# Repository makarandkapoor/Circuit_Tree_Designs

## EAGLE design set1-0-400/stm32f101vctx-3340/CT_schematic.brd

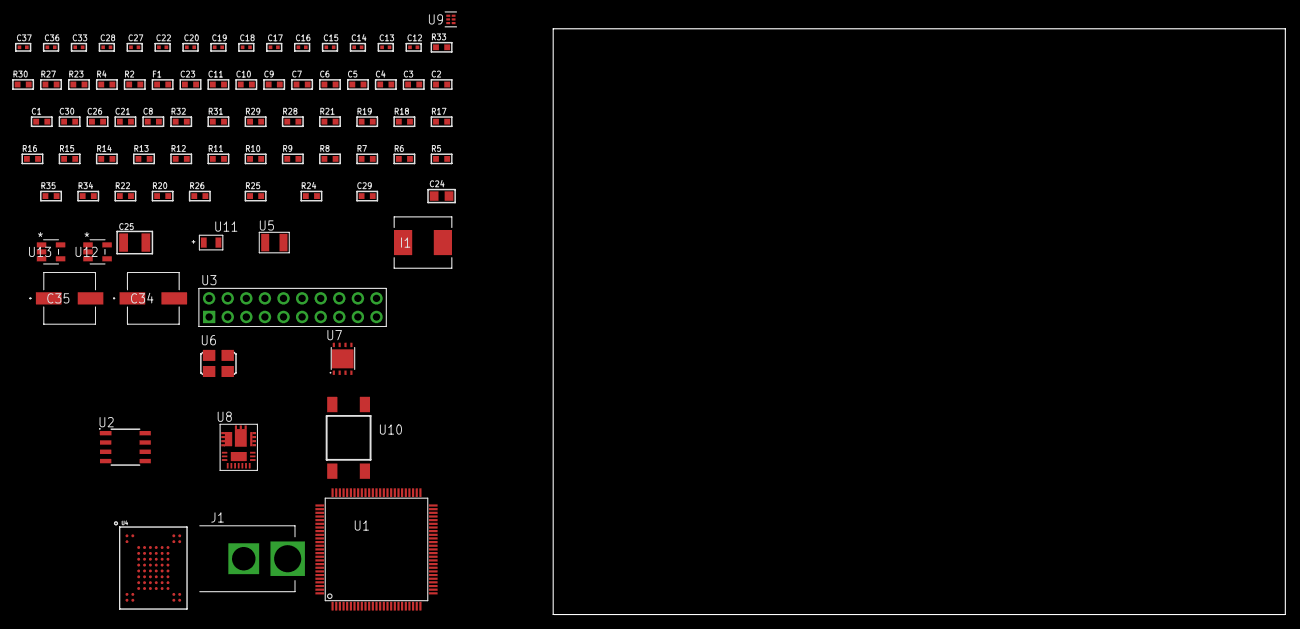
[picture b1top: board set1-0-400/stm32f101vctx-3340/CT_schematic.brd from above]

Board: 2 copper layers, 100.0 x 80.0 mm, 84 parts (0 on the bottom side), 45 nets, no tracks yet.

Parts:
C1, C11: 1e-06; C0603
C2, C3, C4, C5, C6, C7: 1e-07; C0603
C8: 4.7e-06; C0603
C9, C10: 1e-08; C0603
C12, C13: 1e-11; C0402
C14, C22, C36, C37: 1e-08; C0402
C15, C16, C17, C18, C19, C20, C27, C28, C33: 1e-07; C0402
C21, C26: 2.2e-06; C0603
C23: 8e-07; R0603
C24: 1e-05; C0805
C25: 0.0001; C1210
C29: 7.8444498006919e-09; R0603
C30: 2.7e-07; C0603
C34, C35: 0.0001; EXV-9H
F1: 240.0; L0603
I1: 6.8e-07; IND25X25CZ
J1: PJ-037B; PJ-037B_PACKAGE
R2: 1000.0; R0603
R4: 4700.0; R0603
R5, R6, R7, R8, R9, R10, R11, R12, R13, R14, R15, R16, R17, R18, R19, R31, R32: 10000.0; R0603
R20, R22: 100000.0; R0603
R21: 36000.0; R0603
R23: 0.1; R0603
R24: 4030.2416170974; R0603
R25: 719.68600305311; R0603
R26: 64.984347826087; R0603
R27: 130.0; R0603
R28: 39000.0; R0603
R29: 49900.0; R0603
R30: 5600.0; R0603
R33: 9100.0; R0603
R34: 680000.0; R0603
R35: 120000.0; R0603
U1: STM32F101VCT6; LQFP100
U2: AT25M02-SSHD-T; SOIC-8
U3: TST-110-05-T-D-RA
U4: mt29f4g08abbdah4; VFBGA-63
U5: ABS07-32.768KHZ-7-T
U6: ASFL1-25MHZ-NCS; ASFL1
U7: LP2951ACSDX/NOPB; WSON-8
U8: IR3899MTR1PBF
U9: TPS3895ADRYR; SON-6
U10: 4-1437565-2; SW_4-1437565-2
U11: Q65110A2395; LGM67K-G1J2-24-Z
U12, U13: nc7sz125m5x; NC7SZ125M5X

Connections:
CLK_CRYSTAL_U1_8: C12.1, U1.8, U5.1
CLK_CRYSTAL_U1_9: C13.1, U1.9, U5.2
CLK_U1_12: U1.12, U6.3
GND: C1.2, C2.2, C3.2, C4.2, C5.2, C6.2, C7.2, C8.2, C9.2, C10.2, C11.2, C12.2, C13.2, C14.2, C15.2, C16.2, C17.2, C18.2, C19.2, C20.2, C21.2, C22.2, C23.2, C24.2, C26.2, C27.2, C28.2, C33.2, C34.2, C35.2, C36.2, C37.2, J1.2, R2.2, R5.2, R14.2, R22.2, R23.1, R23.2, R25.2, R28.2, R30.2, R33.2, R35.2, U1.10, U1.19, U1.20, U1.27, U1.49, U1.74, U1.99, U2.4, U3.4, U3.6, U3.8, U3.10, U3.12, U3.14, U3.16, U3.18, U3.20, U4.C5, U4.F7, U4.K3, U4.K8, U6.2, U7.3, U7.4, U7.PAD, U8.4, U8.11, U8.17, U9.2, U11.C, U12.2, U12.3, U13.1, U13.3
NET_U1_14: R4.1, U1.14, U13.4
NET_U1_22: C9.1, C10.1, C11.1, F1.1, U1.21, U1.22
NET_U1_94: R5.1, U1.94
NET_U1_98: U10.3, U10.4
NET_U2_3: R6.1, U2.3
NET_U2_7: R8.1, U2.7
NET_U3_3: R9.1, U3.3
NET_U3_7: R11.1, U3.7
NET_U3_19: R14.1, U3.19
NET_U4_C3: R19.1, U4.C3
NET_U4_C6: R16.1, U4.C6
NET_U4_C7: R17.1, U4.C7
NET_U4_C8: R15.1, U4.C8
NET_U4_D4: R18.1, U4.D4
NET_U7_5: R20.1, U7.5
NET_U7_7: R21.2, R22.1, U7.7
NET_U8_1: C29.1, R24.1, R25.1, R26.1, R27.1, U8.1, U8.8
NET_U8_2: C28.1, U8.2
NET_U8_3: C29.2, C30.1, C30.2, U8.3
NET_U8_5: R28.1, U8.5
NET_U8_10: C26.1, U8.10
NET_U8_12: C25.1, I1.1, U8.12
NET_U8_14: C25.2, U8.14
NET_U8_15: R29.1, R30.1, U8.15
NET_U8_ATNET_3: I1.2, R24.2
NET_U8_ATNET_4: C30.2, R26.2
NET_U9_1: R32.1, R33.1, U9.1
NET_U9_3: R34.2, R35.1, U9.3
NET_U9_4: R31.1, U9.4, U12.4, U13.2
NET_U10_1: R2.1, U10.1, U10.2
PROC_SPI1_MISO: U1.31, U2.2
PROC_SPI1_MOSI: U1.32, U2.5
PROC_SPI1_NSS: R7.1, U1.29, U2.1
PROC_SPI1_SCK: U1.30, U2.6
PROC_SYS_JTDI: R10.1, U1.77, U3.5
PROC_SYS_JTDO_TRACESWO: U1.89, U3.13
PROC_SYS_TRACECLK: R12.1, U1.1, U3.9
RST_OUT_U3_SRESET_B: R13.1, U3.15, U12.1
VCC_S1_16V1: C23.1, C27.1, C34.1, C35.1, J1.1, R29.2, U7.8, U8.9
VCC_TIER1_1V8: C17.1, C18.1, C19.1, C20.1, C21.1, C24.1, C36.1, C37.1, R15.2, R16.2, R17.2, R18.2, R19.2, R20.2, R21.1, U4.D3, U4.G4, U4.H8, U4.J6, U7.1, U12.5, U13.5
VCC_TIER1_3V3: C1.1, C2.1, C3.1, C4.1, C5.1, C6.1, C7.1, C8.1, C14.1, C15.1, C16.1, C22.1, C33.1, F1.2, I1.2, R4.2, R6.2, R7.2, R8.2, R9.2, R10.2, R11.2, R12.2, R13.2, R24.2, R31.2, R32.2, R34.1, U1.6, U1.11, U1.28, U1.50, U1.75, U1.100, U2.8, U3.1, U3.2, U6.4, U9.6

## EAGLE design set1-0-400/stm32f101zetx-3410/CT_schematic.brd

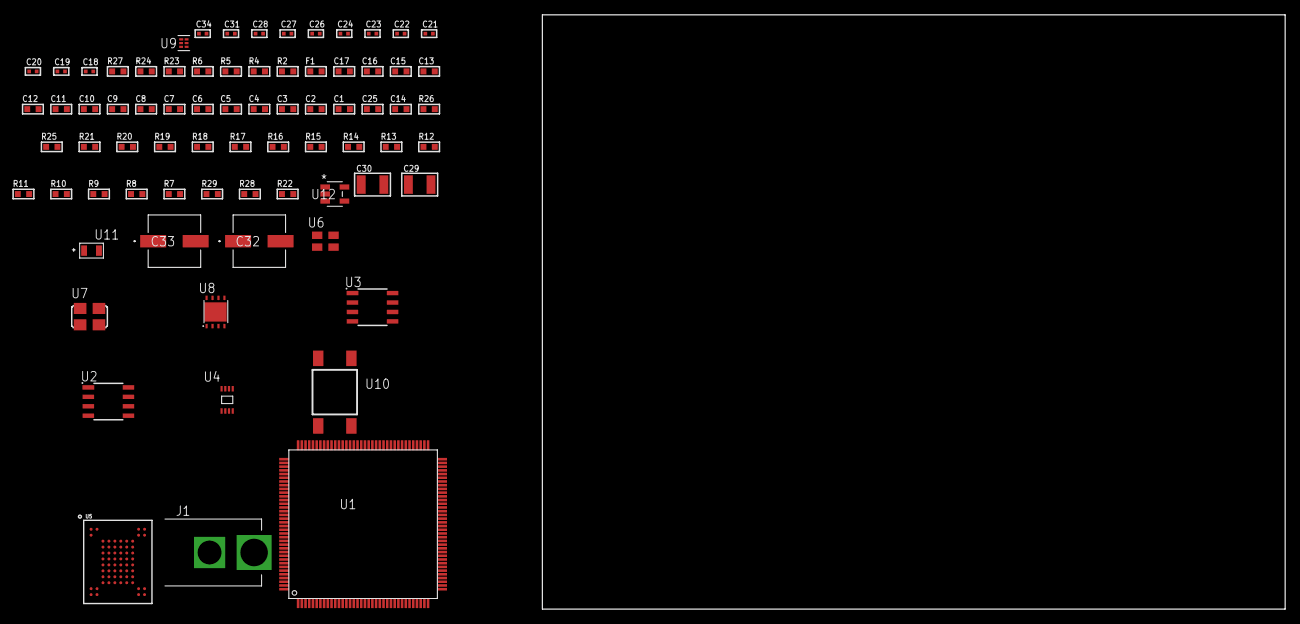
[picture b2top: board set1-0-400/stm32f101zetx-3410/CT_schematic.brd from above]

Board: 2 copper layers, 100.0 x 80.0 mm, 75 parts (0 on the bottom side), 46 nets, no tracks yet.

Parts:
C1, C17: 1e-06; C0603
C2, C3, C4, C5, C6, C7, C8, C9, C10, C11, C12, C13: 1e-07; C0603
C14: 4.7e-06; C0603
C15, C16: 1e-08; C0603
C18, C19, C20, C26, C27, C28, C34: 1e-08; C0402
C21, C22, C23, C24, C31: 1e-07; C0402
C25: 2.2e-06; C0603
C29, C30: 1e-05; C1210
C32, C33: 0.0001; EXV-9H
F1: 240.0; L0603
J1: PJ-037B; PJ-037B_PACKAGE
R2, R24: 1000.0; R0603
R4: 4700.0; R0603
R5, R6: 2200.0; R0603
R7, R8, R9, R10, R11, R12, R13, R14, R15, R16, R17, R18, R19, R20, R21, R25, R26: 10000.0; R0603
R22: 100000.0; R0603
R23: 2231.0; R0603
R27: 9100.0; R0603
R28: 680000.0; R0603
R29: 120000.0; R0603
U1: STM32F101ZETx; LQFP144
U2: AT25040B-SSHL-T; SOIC-8
U3: AT25512N-SH-T; SOIC-8
U4: 24AA64T-I/MNY; TDFN-8/6MM
U5: mt29f4g08abadah4; VFBGA-63
U6: ASEK-32.768KHz-ECST; ASEK
U7: ASFL1-25MHZ-NCS; ASFL1
U8: LP3878SDX-ADJ/NOPB; WSON-8
U9: TPS3895ADRYR; SON-6
U10: 4-1437565-2; SW_4-1437565-2
U11: Q65110A2395; LGM67K-G1J2-24-Z
U12: nc7sz125m5x; NC7SZ125M5X

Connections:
CLK_U1_8: U1.8, U6.3
CLK_U1_23: U1.23, U7.3
GND: C1.2, C2.2, C3.2, C4.2, C5.2, C6.2, C7.2, C8.2, C9.2, C10.2, C11.2, C12.2, C13.2, C14.2, C15.2, C16.2, C17.2, C18.2, C19.2, C20.2, C21.2, C22.2, C23.2, C24.2, C25.2, C26.2, C27.2, C28.2, C29.2, C30.2, C31.2, C32.2, C33.2, C34.2, J1.2, R2.2, R7.2, R24.2, R27.2, R29.2, U1.16, U1.30, U1.31, U1.38, U1.51, U1.61, U1.71, U1.83, U1.94, U1.107, U1.120, U1.130, U1.143, U2.4, U3.4, U4.4, U5.C5, U5.F7, U5.K3, U5.K8, U6.2, U7.2, U8.3, U8.PAD, U9.2, U11.C, U12.1, U12.3
NET_U1_25: R4.1, U1.25, U12.4
NET_U1_33: C15.1, C16.1, C17.1, F1.1, U1.32, U1.33
NET_U1_136: R5.1, U1.136, U4.6
NET_U1_137: R6.1, U1.137, U4.5
NET_U1_138: R7.1, U1.138
NET_U1_142: U10.3, U10.4
NET_U2_3: R8.1, U2.3
NET_U2_7: R10.1, U2.7
NET_U3_3: R11.1, U3.3
NET_U3_7: R13.1, U3.7
NET_U4_1: R14.1, U4.1
NET_U4_2: R15.1, U4.2
NET_U4_3: R16.1, U4.3
NET_U5_C3: R21.1, U5.C3
NET_U5_C8: R17.1, U5.C8
NET_U8_1: C28.1, U8.1
NET_U8_6: R23.2, R24.1, U8.6
NET_U8_8: R22.1, U8.8
NET_U9_1: R26.1, R27.1, U9.1
NET_U9_3: R28.2, R29.1, U9.3
NET_U9_4: R25.1, U9.4, U12.2
NET_U10_1: R2.1, U10.1, U10.2
PROC_FSMC_D0: U1.85, U5.H4
PROC_FSMC_D1: U1.86, U5.J4
PROC_FSMC_D2: U1.114, U5.K4
PROC_FSMC_D3: U1.115, U5.K5
PROC_FSMC_D4: U1.58, U5.K6
PROC_FSMC_D5: U1.59, U5.J7
PROC_FSMC_D6: U1.60, U5.K7
PROC_FSMC_D7: U1.63, U5.J8
PROC_FSMC_NCE2: R18.1, U1.123, U5.C6
PROC_FSMC_NOE: R20.1, U1.118, U5.D4
PROC_FSMC_NWE: R19.1, U1.119, U5.C7
PROC_SPI1_MISO: U1.42, U3.2
PROC_SPI1_MOSI: U1.43, U3.5
PROC_SPI1_NSS: R12.1, U1.40, U3.1
PROC_SPI1_SCK: U1.41, U3.6
PROC_SPI2_MISO: U1.75, U2.2
PROC_SPI2_MOSI: U1.76, U2.5
PROC_SPI2_NSS: R9.1, U1.73, U2.1
PROC_SPI2_SCK: U1.74, U2.6
VCC_S1_13V8: C29.1, C32.1, C33.1, J1.1, R22.2, U8.4
VCC_TIER1_3V3: C1.1, C2.1, C3.1, C4.1, C5.1, C6.1, C7.1, C8.1, C9.1, C10.1, C11.1, C12.1, C13.1, C14.1, C18.1, C19.1, C20.1, C21.1, C22.1, C23.1, C24.1, C25.1, C26.1, C27.1, C30.1, C31.1, C34.1, F1.2, R4.2, R5.2, R6.2, R8.2, R9.2, R10.2, R11.2, R12.2, R13.2, R14.2, R15.2, R16.2, R17.2, R18.2, R19.2, R20.2, R21.2, R23.1, R25.2, R26.2, R28.1, U1.6, U1.17, U1.39, U1.52, U1.62, U1.72, U1.84, U1.95, U1.108, U1.121, U1.131, U1.144, U2.8, U3.8, U4.7, U4.8, U5.D3, U5.G4, U5.H8, U5.J6, U6.4, U7.4, U8.5, U9.6, U12.5

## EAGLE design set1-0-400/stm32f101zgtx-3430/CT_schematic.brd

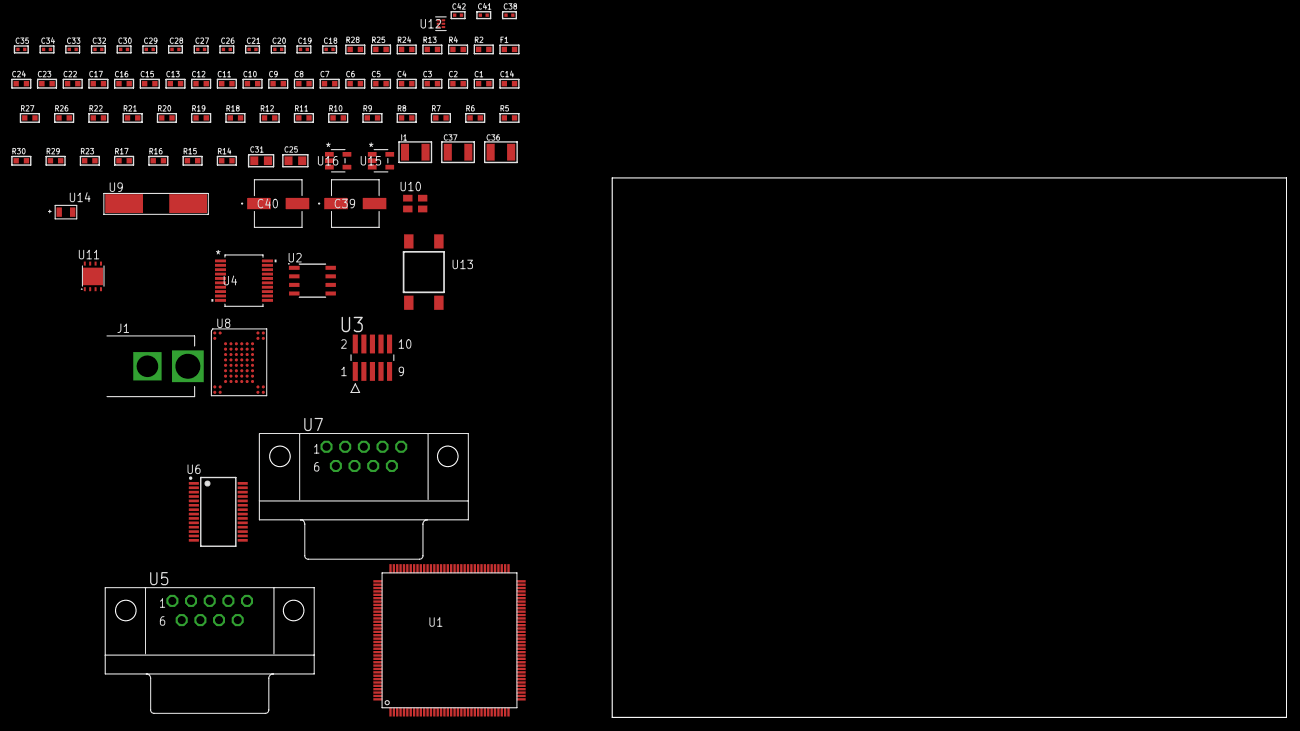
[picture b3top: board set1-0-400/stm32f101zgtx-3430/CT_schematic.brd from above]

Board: 2 copper layers, 100.0 x 80.0 mm, 89 parts (0 on the bottom side), 69 nets, no tracks yet.

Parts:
C1, C17, C22, C23, C24: 1e-06; C0603
C2, C3, C4, C5, C6, C7, C8, C9, C10, C11, C12, C13: 1e-07; C0603
C14: 4.7e-06; C0603
C15, C16: 1e-08; C0603
C18, C19: 1e-11; C0402
C20, C34, C35, C41, C42: 1e-08; C0402
C21, C26, C27, C28, C29, C30, C32, C33, C38: 1e-07; C0402
C25: 4.7e-06; C0805
C31: 1e-05; C0805
C36, C37: 1e-05; C1210
C39, C40: 0.0001; EXV-9H
F1: 240.0; L0603
I1: 1.5e-05; L1210
J1: PJ-037B; PJ-037B_PACKAGE
R2, R25: 1000.0; R0603
R4: 4700.0; R0603
R5, R6, R7, R8, R9, R10, R11, R12, R18, R19, R20, R21, R22, R26, R27: 10000.0; R0603
R13: 5.0; R0603
R14, R15, R16, R17, R23: 100000.0; R0603
R24: 2231.0; R0603
R28: 9100.0; R0603
R29: 680000.0; R0603
R30: 120000.0; R0603
U1: STM32F101ZGTx; LQFP144
U2: AT25128B-SSHL-T; SOIC-8
U3: FTSH-105-01-L-DV-K; SAMTEC_FTSH-105-01-L-DV-K
U4: MAX3218EAP+T; SSOP-20
U5, U7: 182-009-113R531; 182-009-MALE
U6: ST3241EBPR; SSOP-28
U8: TH58NVG3S0HBAI4
U9: ABLS-25.000MHZ-B2F-T
U10: ASEK-32.768KHz-ECST; ASEK
U11: LP3878SDX-ADJ/NOPB; WSON-8
U12: TPS3895ADRYR; SON-6
U13: 4-1437565-2; SW_4-1437565-2
U14: Q65110A2395; LGM67K-G1J2-24-Z
U15, U16: nc7sz125m5x; NC7SZ125M5X

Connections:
CLK_CRYSTAL_U1_23: C18.1, U1.23, U9.1
CLK_CRYSTAL_U1_24: C19.1, U1.24, U9.2
CLK_U1_8: U1.8, U10.3
GND: C1.2, C2.2, C3.2, C4.2, C5.2, C6.2, C7.2, C8.2, C9.2, C10.2, C11.2, C12.2, C13.2, C14.2, C15.2, C16.2, C17.2, C18.2, C19.2, C20.2, C21.2, C22.2, C23.2, C24.2, C26.2, C29.2, C30.2, C31.2, C32.2, C33.2, C34.2, C35.2, C36.2, C37.2, C38.2, C39.2, C40.2, C41.2, C42.2, J1.2, R2.2, R5.2, R12.2, R13.2, R25.2, R28.2, R30.2, U1.16, U1.30, U1.31, U1.38, U1.51, U1.61, U1.71, U1.83, U1.94, U1.107, U1.120, U1.130, U1.143, U2.4, U3.3, U3.5, U4.5, U4.17, U4.20, U5.5, U6.23, U6.25, U7.5, U8.C5, U8.K3, U8.K8, U10.2, U11.3, U11.PAD, U12.2, U14.C, U15.2, U15.3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
NET_U1_25: R4.1, U1.25, U16.4
NET_U1_33: C15.1, C16.1, C17.1, F1.1, U1.32, U1.33
NET_U1_138: R5.1, U1.138
NET_U1_142: U13.3, U13.4
NET_U2_3: R6.1, U2.3
NET_U2_7: R8.1, U2.7
NET_U3_2: R11.1, U3.2
NET_U3_9: R13.1, U3.9
NET_U4_1: I1.1, U4.1
NET_U4_2: R14.1, U4.2
NET_U4_3: R15.1, U4.3
NET_U4_4: R16.1, U4.4
NET_U4_15: C24.1, U4.15
NET_U4_16: C25.2, U4.16
NET_U4_18: C25.1, U4.18
NET_U4_19: C23.1, U4.19
NET_U5_2: U4.12, U5.2
NET_U5_3: U4.14, U5.3
NET_U5_7: U4.11, U5.7
NET_U5_8: U4.13, U5.8
NET_U6_1: C28.1, U6.1
NET_U6_2: C28.2, U6.2
NET_U6_3: C30.1, U6.3
NET_U6_22: R17.1, U6.22
NET_U6_24: C27.2, U6.24
NET_U6_27: C29.1, U6.27
NET_U6_28: C27.1, U6.28
NET_U7_2: U6.4, U7.2
NET_U7_3: U6.9, U7.3
NET_U7_7: U6.5, U7.7
NET_U7_8: U6.10, U7.8
NET_U8_C3: R21.1, U8.C3
NET_U8_C8: R22.1, U8.C8
NET_U11_1: C35.1, U11.1
NET_U11_6: R24.2, R25.1, U11.6
NET_U11_8: R23.1, U11.8
NET_U12_1: R27.1, R28.1, U12.1
NET_U12_3: R29.2, R30.1, U12.3
NET_U12_4: R26.1, U12.4, U15.4, U16.2
NET_U13_1: R2.1, U13.1, U13.2
PROC_FSMC_D0: U1.85, U8.H4
PROC_FSMC_D1: U1.86, U8.J4
PROC_FSMC_D2: U1.114, U8.K4
PROC_FSMC_D3: U1.115, U8.K5
PROC_FSMC_D4: U1.58, U8.K6
PROC_FSMC_D5: U1.59, U8.J7
PROC_FSMC_D6: U1.60, U8.K7
PROC_FSMC_D7: U1.63, U8.J8
PROC_FSMC_NCE2: R18.1, U1.123, U8.C6
PROC_FSMC_NOE: R19.1, U1.118, U8.D4
PROC_FSMC_NWE: R20.1, U1.119, U8.C7
PROC_SPI1_MISO: U1.42, U2.2
PROC_SPI1_MOSI: U1.43, U2.5
PROC_SPI1_NSS: R7.1, U1.40, U2.1
PROC_SPI1_SCK: U1.41, U2.6
PROC_SYS_JTDI: R10.1, U1.110, U3.8
PROC_SYS_JTDO_TRACESWO: U1.133, U3.6
PROC_SYS_TRACECLK: R12.1, U1.1, U3.4
PROC_UART4_RX: U1.112, U4.9
PROC_UART4_TX: U1.111, U4.7
PROC_UART5_RX: U1.116, U6.19
PROC_UART5_TX: U1.113, U6.14
RST_OUT_U3_JTAG_RST_B: R9.1, U3.10, U15.1
VCC_S1_14V8: C36.1, C39.1, C40.1, J1.1, R23.2, U11.4
VCC_TIER1_3V3: C1.1, C2.1, C3.1, C4.1, C5.1, C6.1, C7.1, C8.1, C9.1, C10.1, C11.1, C12.1, C13.1, C14.1, C20.1, C21.1, C22.1, C26.1, C31.1, C32.1, C33.1, C34.1, C37.1, C38.1, C41.1, C42.1, F1.2, I1.2, R4.2, R6.2, R7.2, R8.2, R9.2, R10.2, R11.2, R14.2, R15.2, R16.2, R17.2, R18.2, R19.2, R20.2, R21.2, R22.2, R24.1, R26.2, R27.2, R29.1, U1.6, U1.17, U1.39, U1.52, U1.62, U1.72, U1.84, U1.95, U1.108, U1.121, U1.131, U1.144, U2.8, U3.1, U4.6, U6.26, U8.H8, U8.J6, U10.4, U11.5, U12.6, U15.5, U16.5

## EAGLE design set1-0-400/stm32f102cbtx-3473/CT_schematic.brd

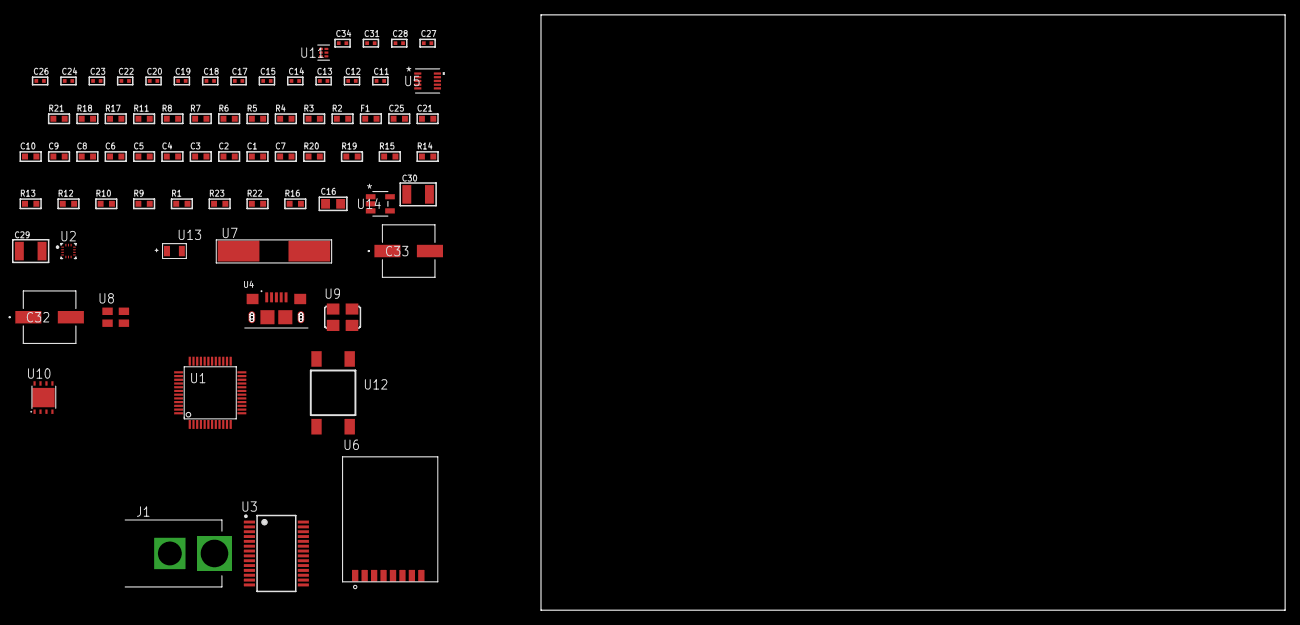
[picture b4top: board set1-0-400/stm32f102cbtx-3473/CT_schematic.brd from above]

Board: 2 copper layers, 73 parts (0 on the bottom side), 40 nets, no tracks yet.

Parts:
C1, C10, C21, C25: 1e-06; C0603
C2, C3, C4, C5, C6: 1e-07; C0603
C7: 4.7e-06; C0603
C8, C9: 1e-08; C0603
C11, C12: 1e-11; C0402
C13, C14, C15, C17, C18, C19, C20, C22, C23, C24, C31: 1e-07; C0402
C16: 4.7e-06; C0805
C26, C27, C28, C34: 1e-08; C0402
C29, C30: 1e-05; C1210
C32, C33: 0.0001; EXV-9H
F1: 240.0; L0603
J1: PJ-037B; PJ-037B_PACKAGE
R1, R9, R10, R12, R13, R14, R15, R19, R20: 10000.0; R0603
R2, R18: 1000.0; R0603
R3: 1600.5; R0603
R4, R11: 4700.0; R0603
R5, R6, R7, R8: 2200.0; R0603
R16: 100000.0; R0603
R17: 2231.0; R0603
R21: 9100.0; R0603
R22: 680000.0; R0603
R23: 120000.0; R0603
U1: STM32F102CBT6; LQFP48
U2: BMC150; LGA14R35P5X6_200X200X100
U3: FT232RL-REEL; SSOP-28
U4: 10118193-0001LF; FCI_10118193-0001LF
U5: MAG3110FCR1; DFN-10
U6: RFM75-S
U7: ABLS-25.000MHZ-B2F-T
U8: ASEK-32.768KHz-ECST; ASEK
U9: ASFL1-12MHZ-NCS; ASFL1
U10: LP3878SDX-ADJ/NOPB; WSON-8
U11: TPS3895ADRYR; SON-6
U12: 4-1437565-2; SW_4-1437565-2
U13: Q65110A2395; LGM67K-G1J2-24-Z
U14: nc7sz125m5x; NC7SZ125M5X

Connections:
CLK_CRYSTAL_U1_5: C11.1, U1.5, U7.1
CLK_CRYSTAL_U1_6: C12.1, U1.6, U7.2
CLK_U1_3: U1.3, U8.3
CLK_U3_27: U3.27, U9.3
GND: C1.2, C2.2, C3.2, C4.2, C5.2, C6.2, C7.2, C8.2, C9.2, C10.2, C11.2, C12.2, C13.2, C14.2, C15.2, C16.2, C17.2, C18.2, C19.2, C20.2, C21.2, C22.2, C23.2, C24.2, C25.2, C26.2, C27.2, C28.2, C29.2, C30.2, C31.2, C32.2, C33.2, C34.2, J1.2, R2.2, R9.2, R13.2, R18.2, R21.2, R23.2, U1.8, U1.23, U1.35, U1.47, U2.1, U2.6, U2.7, U2.9, U3.7, U3.18, U3.21, U3.25, U3.26, U4.5, U4.6, U4.7, U4.8, U4.9, U5.5, U5.10, U6.1, U8.2, U9.2, U10.3, U10.PAD, U11.2, U13.C, U14.1, U14.3
NET_U1_7: R4.1, U1.7, U14.4
NET_U1_9: C8.1, C9.1, C10.1, F1.1, U1.9
NET_U1_21: R7.1, U1.21, U2.11
NET_U1_22: R8.1, U1.22, U2.14
NET_U1_42: R5.1, U1.42, U5.7
NET_U1_43: R6.1, U1.43, U5.6
NET_U1_44: R9.1, U1.44
NET_U1_45: R3.1, U1.45, U13.A
NET_U1_46: R1.1, U1.46, U12.3, U12.4
NET_U3_14: R12.1, U3.14
NET_U3_17: C17.1, U3.17
NET_U3_19: R13.1, U3.19
NET_U4_1: R11.1, U4.1
NET_U4_2: U3.16, U4.2
NET_U4_3: U3.15, U4.3
NET_U5_1: C19.1, U5.1
NET_U5_4: C22.1, U5.4
NET_U6_3: R14.1, U6.3
NET_U10_1: C28.1, U10.1
NET_U10_6: R17.2, R18.1, U10.6
NET_U10_8: R16.1, U10.8
NET_U11_1: R20.1, R21.1, U11.1
NET_U11_3: R22.2, R23.1, U11.3
NET_U11_4: R19.1, U11.4, U14.2
NET_U12_1: R2.1, U12.1, U12.2
PROC_SPI1_MISO: U1.16, U6.7
PROC_SPI1_MOSI: U1.17, U6.6
PROC_SPI1_NSS: R15.1, U1.14, U6.4
PROC_SPI1_SCK: U1.15, U6.5
PROC_USART1_CTS: U1.32, U3.3
PROC_USART1_RTS: U1.33, U3.11
PROC_USART1_RX: U1.31, U3.1
PROC_USART1_TX: U1.30, U3.5
VCC_S1_13V2: C29.1, C32.1, C33.1, J1.1, R16.2, U10.4
VCC_TIER1_3V3: C1.1, C2.1, C3.1, C4.1, C5.1, C6.1, C7.1, C13.1, C14.1, C15.1, C16.1, C18.1, C20.1, C21.1, C23.1, C24.1, C25.1, C26.1, C27.1, C30.1, C31.1, C34.1, F1.2, R1.2, R3.2, R4.2, R5.2, R6.2, R7.2, R8.2, R10.1, R10.2, R12.2, R14.2, R15.2, R17.1, R19.2, R20.2, R22.1, U1.1, U1.24, U1.36, U1.48, U2.8, U2.10, U2.12, U2.13, U3.4, U3.20, U5.2, U5.8, U6.2, U8.4, U9.4, U10.5, U11.6, U14.5

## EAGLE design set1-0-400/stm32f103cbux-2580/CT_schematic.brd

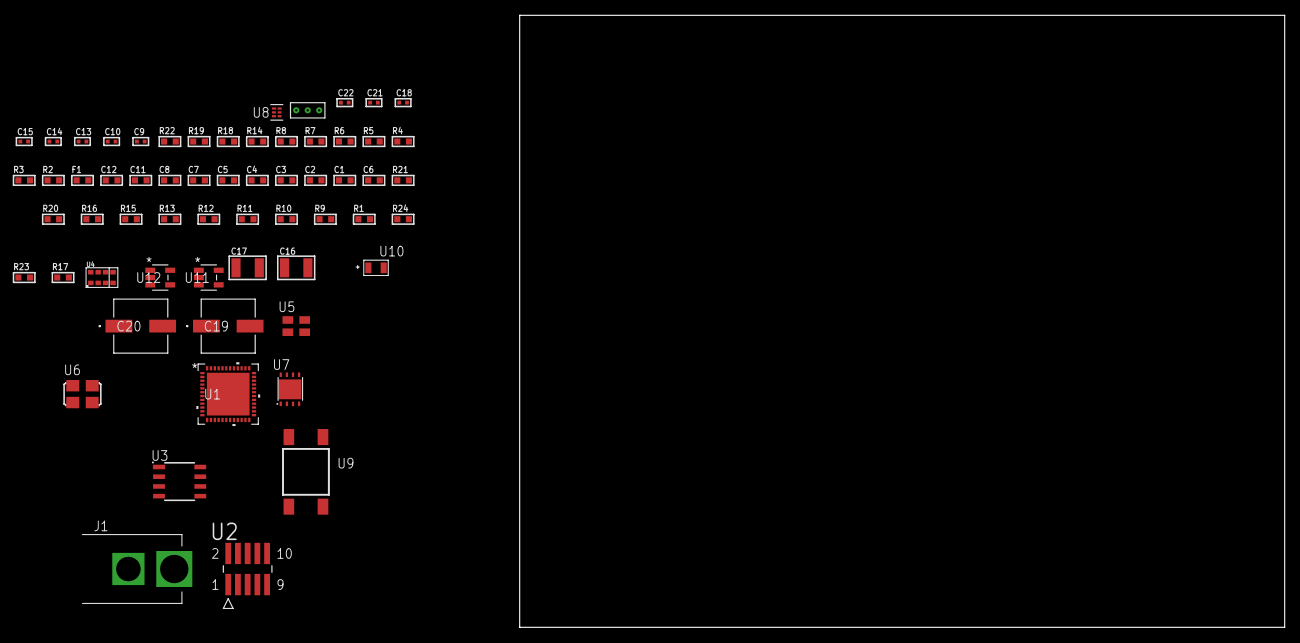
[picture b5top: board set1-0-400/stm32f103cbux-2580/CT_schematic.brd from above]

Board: 2 copper layers, 100.0 x 80.0 mm, 61 parts (0 on the bottom side), 31 nets, no tracks yet.

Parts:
C1, C8, C11, C12: 1e-06; C0603
C2, C3, C4, C5: 1e-07; C0603
C6: 4.7e-06; C0603
C7: 1e-08; C0603
C9, C18: 1e-07; C0402
C10, C13, C14, C15, C21, C22: 1e-08; C0402
C16, C17: 1e-05; C1210
C19, C20: 0.0001; EXV-9H
F1: 240.0; L0603
J1: PJ-037B; PJ-037B_PACKAGE
R1, R9, R10, R11, R12, R13, R15, R16, R20, R21: 10000.0; R0603
R2, R19: 1000.0; R0603
R3: 1600.5; R0603
R4: 4700.0; R0603
R5, R6, R7, R8: 2200.0; R0603
R14: 5.0; R0603
R17: 100000.0; R0603
R18: 2231.0; R0603
R22: 9100.0; R0603
R23: 680000.0; R0603
R24: 120000.0; R0603
U1: stm32f103cbu6; UFQFPN48
U2: FTSH-105-01-L-DV-K; SAMTEC_FTSH-105-01-L-DV-K
U3: M24M02-DRMN6TP; SOIC-8
U4: TMD27711; SMD-8
U5: ASEK-32.768KHz-ECST; ASEK
U6: ASFL1-25MHZ-NCS; ASFL1
U7: LP3878SDX-ADJ/NOPB; WSON-8
U8: TPS3895ADRYR; SON-6
U9: 4-1437565-2; SW_4-1437565-2
U10: Q65110A2395; LGM67K-G1J2-24-Z
U11, U12: nc7sz125m5x; NC7SZ125M5X
U13: Dummy; DUMMY_PACKAGE_131

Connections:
CLK_U1_3: U1.3, U5.3
CLK_U1_5: U1.5, U6.3
GND: C1.2, C2.2, C3.2, C4.2, C5.2, C6.2, C7.2, C8.2, C9.2, C10.2, C11.2, C12.2, C13.2, C14.2, C15.2, C16.2, C17.2, C18.2, C19.2, C20.2, C21.2, C22.2, J1.2, R2.2, R9.2, R13.2, R14.2, R15.2, R19.2, R22.2, R24.2, U1.8, U1.23, U1.35, U1.47, U1.49, U2.3, U2.5, U3.4, U4.3, U5.2, U6.2, U7.3, U7.PAD, U8.2, U10.C, U11.2, U11.3, U12.1, U12.3, U13.1
NET_U1_7: R4.1, U1.7, U12.4
NET_U1_9: C7.1, C8.1, F1.1, U1.9
NET_U1_21: R7.1, U1.21, U3.6
NET_U1_22: R8.1, U1.22, U3.5
NET_U1_42: R5.1, U1.42, U4.2
NET_U1_43: R6.1, U1.43, U4.8
NET_U1_44: R9.1, U1.44
NET_U1_45: R3.1, U1.45, U10.A
NET_U1_46: R1.1, U1.46, U9.3, U9.4
NET_U2_2: R12.1, U2.2
NET_U2_4: R13.1, U2.4
NET_U2_9: R14.1, U2.9
NET_U3_3: R15.1, U3.3
NET_U4_7: R16.1, U4.7
NET_U7_1: C15.1, U7.1
NET_U7_6: R18.2, R19.1, U7.6
NET_U7_8: R17.1, U7.8
NET_U8_1: R21.1, R22.1, U8.1
NET_U8_3: R23.2, R24.1, U8.3
NET_U8_4: R20.1, U8.4, U11.4, U12.2
NET_U9_1: R2.1, U9.1, U9.2
PROC_SYS_JTDI: R11.1, U1.38, U2.8
PROC_SYS_JTDO_TRACESWO: U1.39, U2.6
PROC_TIM1_CH2: U1.30, U13.2
PROC_TIM1_CH4: U1.32, U13.3
RST_OUT_U2_JTAG_RST_B: R10.1, U2.10, U11.1
VCC_S1_15V5: C16.1, C19.1, C20.1, J1.1, R17.2, U7.4
VCC_TIER1_3V3: C1.1, C2.1, C3.1, C4.1, C5.1, C6.1, C9.1, C10.1, C11.1, C12.1, C13.1, C14.1, C17.1, C18.1, C21.1, C22.1, F1.2, R1.2, R3.2, R4.2, R5.2, R6.2, R7.2, R8.2, R10.2, R11.2, R12.2, R16.2, R18.1, R20.2, R21.2, R23.1, U1.1, U1.24, U1.36, U1.48, U2.1, U3.8, U4.1, U4.4, U5.4, U6.4, U7.5, U8.6, U11.5, U12.5

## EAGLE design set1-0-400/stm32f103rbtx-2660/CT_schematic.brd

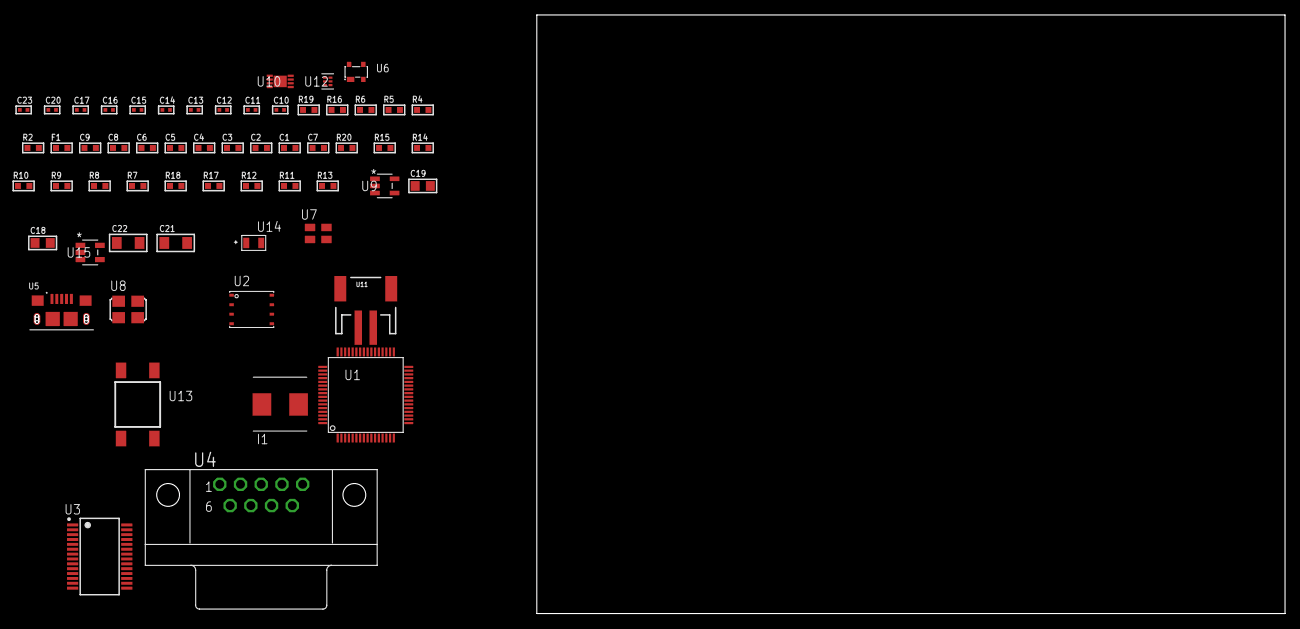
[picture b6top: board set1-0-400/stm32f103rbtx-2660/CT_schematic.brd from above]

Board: 2 copper layers, 167.1 x 80.0 mm, 58 parts (0 on the bottom side), 41 nets, no tracks yet.

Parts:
C1, C9: 1e-06; C0603
C2, C3, C4, C5, C6: 1e-07; C0603
C7: 4.7e-06; C0603
C8: 1e-08; C0603
C10, C16, C17, C23: 1e-08; C0402
C11, C12, C13, C14, C15, C20: 1e-07; C0402
C18, C19: 1e-05; C0805
C21, C22: 1e-05; C1206
F1: 240.0; L0603
I1: 2e-06; WE-HCI_7030/7040/7050
R2: 1000.0; R0603
R4: 4700.0; R0603
R5, R6: 2200.0; R0603
R7, R8, R9, R10, R14, R15, R20: 10000.0; R0603
R11: 100000.0; R0603
R12: 220000.0; R0603
R13: 1000000.0; R0603
R16: 9100.0; R0603
R17: 680000.0; R0603
R18: 120000.0; R0603
R19: 2000.0; R0603
U1: stm32f103rbt7; LQFP64
U2: 24AA512-I/MF; DFN8-S
U3: ST3241EBPR; SSOP-28
U4: 182-009-113R531; 182-009-MALE
U5: 10118193-0001LF; FCI_10118193-0001LF
U6: prtr5v0u2ax; SOT143B
U7: ASEK-32.768KHz-ECST; ASEK
U8: ASFL1-25MHZ-NCS; ASFL1
U9: ltc3406es5; TSOT-23-5
U10: MCP73831T-2ACI/MC; DFN8_2X3MC
U11: S2B-PH-SM4-TB(LF)(SN); JST-2-SMD
U12: TPS3895ADRYR; SON-6
U13: 4-1437565-2; SW_4-1437565-2
U14: Q65110A2395; LGM67K-G1J2-24-Z
U15: nc7sz125m5x; NC7SZ125M5X

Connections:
CLK_U1_3: U1.3, U7.3
CLK_U1_5: U1.5, U8.3
GND: C1.2, C2.2, C3.2, C4.2, C5.2, C6.2, C7.2, C8.2, C9.2, C10.2, C11.2, C14.2, C15.2, C16.2, C17.2, C18.2, C19.1, C19.2, C20.2, C21.2, C22.2, C23.2, R2.2, R7.2, R8.2, R12.2, R16.2, R18.2, R19.2, U1.12, U1.18, U1.31, U1.47, U1.63, U2.4, U2.7, U3.23, U3.25, U4.5, U5.5, U5.6, U5.7, U5.8, U5.9, U6.1, U7.2, U8.2, U9.2, U10.6, U10.9, U11.2, U12.2, U14.C, U15.1, U15.3
INPUT_USBPOWER_5V: C21.1, R20.2, U5.1, U6.4, U10.1, U10.2
NET_U1_7: R4.1, U1.7, U15.4
NET_U1_13: C8.1, C9.1, F1.1, U1.13
NET_U1_58: R5.1, U1.58, U2.6
NET_U1_59: R6.1, U1.59, U2.5
NET_U1_60: R7.1, U1.60
NET_U1_62: U13.3, U13.4
NET_U2_1: R8.1, U2.1
NET_U2_2: R9.1, U2.2
NET_U2_3: R10.1, U2.3
NET_U3_1: C13.1, U3.1
NET_U3_2: C13.2, U3.2
NET_U3_3: C15.1, U3.3
NET_U3_22: R11.1, U3.22
NET_U3_24: C12.2, U3.24
NET_U3_27: C14.1, U3.27
NET_U3_28: C12.1, U3.28
NET_U4_2: U3.4, U4.2
NET_U4_3: U3.9, U4.3
NET_U4_7: U3.5, U4.7
NET_U4_8: U3.10, U4.8
NET_U9_3: I1.1, U9.3
NET_U9_5: R12.1, R13.1, U9.5
NET_U9_ATNET_3: I1.2, R13.2
NET_U10_5: R20.1, U10.5
NET_U10_8: R19.1, U10.8
NET_U12_1: R15.1, R16.1, U12.1
NET_U12_3: R17.2, R18.1, U12.3
NET_U12_4: R14.1, U12.4, U15.2
NET_U13_1: R2.1, U13.1, U13.2
PROC_USART2_CTS: U1.14, U3.13
PROC_USART2_RTS: U1.15, U3.18
PROC_USART2_RX: U1.17, U3.19
PROC_USART2_TX: U1.16, U3.14
PROC_USB_DM: U1.44, U5.2, U6.3
PROC_USB_DP: U1.45, U5.3, U6.2
VCC_S1_3V7: C18.1, C22.1, U9.4, U10.3, U10.4, U11.1
VCC_TIER1_3V3: C1.1, C2.1, C3.1, C4.1, C5.1, C6.1, C7.1, C10.1, C11.1, C16.1, C17.1, C19.2, C20.1, C23.1, F1.2, I1.2, R4.2, R5.2, R6.2, R9.2, R10.2, R11.2, R13.2, R14.2, R15.2, R17.1, U1.1, U1.19, U1.32, U1.48, U1.64, U2.8, U3.26, U7.4, U8.4, U12.6, U15.5

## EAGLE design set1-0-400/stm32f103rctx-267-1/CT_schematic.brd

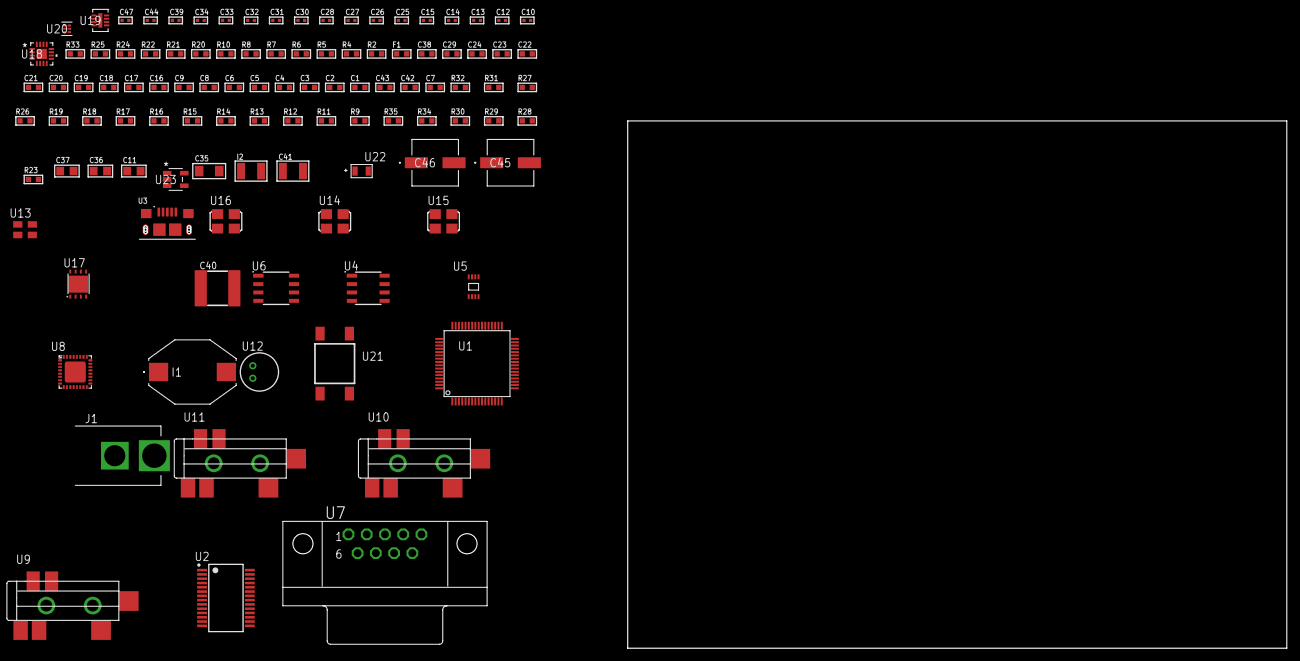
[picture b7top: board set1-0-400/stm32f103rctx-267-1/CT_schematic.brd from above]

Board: 2 copper layers, 107 parts (0 on the bottom side), 70 nets, no tracks yet.

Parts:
C1, C9, C16, C17, C18, C19, C20, C21, C22, C23, C24, C29, C38: 1e-06; C0603
C2, C3, C4, C5, C6: 1e-07; C0603
C7: 4.7e-06; C0603
C8: 1e-08; C0603
C10, C12, C13, C25, C26, C27, C28, C39, C44: 1e-07; C0402
C11: 4.7e-06; C0805
C14, C15, C30, C31, C32, C33, C34, C47: 1e-08; C0402
C35: 1e-05; C1206
C36, C37: 1e-05; C0805
C40: 6.8e-05; 2220
C41: 1e-05; C1210
C42: 2.2e-06; C0603
C43: 2.2e-07; C0603
C45, C46: 0.0001; EXV-9H
F1: 240.0; L0603
I1: 2.2e-06; IND_PM3316
I2: 1e-05; L1210
J1: PJ-037B; PJ-037B_PACKAGE
R2, R25: 1000.0; R0603
R4, R10: 4700.0; R0603
R5, R6, R7, R8: 2200.0; R0603
R9, R11, R12, R13, R14, R15, R16, R17, R18, R19, R31, R32: 10000.0; R0603
R20: 120.0; R0603
R21, R22: 1270.0; R0603
R23, R29: 100000.0; R0603
R24: 200.0; R0603
R26: 20000.0; R0603
R27: 91000.0; R0603
R28: 300000.0; R0603
R30: 560000.0; R0603
R33: 9100.0; R0603
R34: 680000.0; R0603
R35: 120000.0; R0603
U1: stm32f103rct7; LQFP64
U2: FT232RL-REEL; SSOP-28
U3: 10118193-0001LF; FCI_10118193-0001LF
U4: AT24C02D-SSHM-T; AT24C02D
U5: 24AA64T-I/MNY; TDFN-8/6MM
U6: MCP2562-E/SN; SOIC-8
U7: 182-009-113R531; 182-009-MALE
U8: SGTL5000XNAA3; QFN-32
U9, U10, U11: SJ-43515TS-SMT-TR
U12: WM-64PCT; WM-64PC
U13: ASEK-32.768KHz-ECST; ASEK
U14: ASFL1-12MHZ-NCS; ASFL1
U15: ASFL-24.57MHZ-NCS; ASFL1
U16: ASFL1-25MHZ-NCS; ASFL1
U17: LP3878SDX-ADJ/NOPB; WSON-8
U18: LTC3601EUD#PBF; QFN-16_EP
U19: LT3494AEDDB#TRMPBF; DFN-8_DDB
U20: TPS3895ADRYR; SON-6
U21: 4-1437565-2; SW_4-1437565-2
U22: Q65110A2395; LGM67K-G1J2-24-Z
U23: nc7sz125m5x; NC7SZ125M5X

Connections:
CLK_U1_3: U1.3, U13.3
CLK_U1_5: U1.5, U16.3
CLK_U2_27: U2.27, U14.3
CLK_U8_21: U8.21, U15.3
GND: C1.2, C2.2, C3.2, C4.2, C5.2, C6.2, C7.2, C8.2, C9.2, C10.2, C11.2, C12.2, C13.2, C14.2, C15.2, C16.2, C17.2, C25.2, C26.2, C27.2, C28.2, C29.2, C30.2, C31.2, C32.2, C33.2, C34.2, C35.2, C36.2, C37.2, C38.2, C40.1, C40.2, C41.2, C42.2, C43.2, C44.2, C45.2, C46.2, C47.2, J1.2, R2.2, R9.2, R12.2, R13.2, R15.2, R16.2, R17.2, R22.2, R25.2, R26.2, R28.2, R33.2, R35.2, U1.12, U1.18, U1.31, U1.47, U1.63, U2.7, U2.18, U2.21, U2.25, U2.26, U3.5, U3.6, U3.7, U3.8, U3.9, U4.4, U5.4, U5.7, U6.2, U6.8, U7.5, U8.1, U8.3, U8.7, U8.EXP, U10.1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
NET_U1_7: R4.1, U1.7, U23.4
NET_U1_13: C8.1, C9.1, F1.1, U1.13
NET_U1_29: R7.1, U1.29, U4.6
NET_U1_30: R8.1, U1.30, U4.5
NET_U1_58: R5.1, U1.58, U5.6
NET_U1_59: R6.1, U1.59, U5.5
NET_U1_60: R9.1, U1.60
NET_U1_62: U21.3, U21.4
NET_U2_14: R11.1, U2.14
NET_U2_17: C12.1, U2.17
NET_U2_19: R12.1, U2.19
NET_U3_1: R10.1, U3.1
NET_U3_2: U2.16, U3.2
NET_U3_3: U2.15, U3.3
NET_U4_1: R14.1, U4.1
NET_U4_2: R15.1, U4.2
NET_U4_3: R16.1, U4.3
NET_U4_7: R13.1, U4.7
NET_U5_1: R17.1, U5.1
NET_U5_2: R18.1, U5.2
NET_U5_3: R19.1, U5.3
NET_U6_6: R20.2, U6.6
NET_U7_2: R20.2, U6.6, U7.2
NET_U7_3: R20.1, U6.7, U7.3
NET_U8_10: C28.1, U8.10
NET_U8_29: R21.1, U8.29
NET_U8_31: R22.1, U8.31
NET_U9_1: U8.4, U9.1
NET_U9_2: U8.2, U9.2
NET_U9_5: U8.6, U9.5
NET_U10_2: C19.1, U10.2
NET_U10_5: C18.1, U10.5
NET_U11_2: C21.1, C22.1, U11.2
NET_U11_5: C20.1, U11.5
NET_U11_13: C21.2, C22.2
NET_U12_1: C23.1, C24.1, C29.1, U8.16, U12.1
NET_U12_15: C23.2, C24.2
NET_U17_1: C34.1, U17.1
NET_U17_6: R24.2, R25.1, U17.6
NET_U17_8: R23.1, U17.8
NET_U18_3: C39.2, I1.1, U18.3, U18.4
NET_U18_6: C39.1, U18.6
NET_U18_7: C38.1, U18.7, U18.12
NET_U18_10: R28.1, U18.10
NET_U18_11: R26.1, R27.1, U18.11
NET_U18_ATNET_3: I1.2, R27.2
NET_U19_1: I2.1, U19.1
NET_U19_5: R29.1, U19.5
NET_U19_6: R30.1, U19.6
NET_U19_8: C43.1, U19.8
NET_U20_1: R32.1, R33.1, U20.1
NET_U20_3: R34.2, R35.1, U20.3
NET_U20_4: R31.1, U20.4, U23.2
NET_U21_1: R2.1, U21.1, U21.2
PROC_CAN_RX: U1.44, U6.4
PROC_CAN_TX: U1.45, U6.1
PROC_I2S2_CK: U1.34, U8.24
PROC_I2S2_SD: U1.36, U8.26
PROC_I2S2_WS: U1.33, U8.23
PROC_UART4_RX: U1.52, U2.1
PROC_UART4_TX: U1.51, U2.5
VCC_S1_4V8: C35.1, C37.1, C41.1, C45.1, C46.1, I2.2, J1.1, R23.2, R29.2, U17.4, U18.15, U18.16, U19.3, U19.4
VCC_TIER1_1V2: C25.1, C36.1, R24.1, U8.30, U17.5
VCC_TIER1_3V3: C1.1, C2.1, C3.1, C4.1, C5.1, C6.1, C7.1, C10.1, C11.1, C13.1, C14.1, C15.1, C17.1, C26.1, C27.1, C30.1, C31.1, C32.1, C33.1, C40.2, C44.1, C47.1, F1.2, I1.2, R4.2, R5.2, R6.2, R7.2, R8.2, R11.2, R14.2, R18.2, R19.2, R21.2, R27.2, R31.2, R32.2, R34.1, U1.1, U1.19, U1.32, U1.48, U1.64, U2.4, U2.20, U4.8, U5.8, U6.5, U8.5, U8.20, U13.4, U14.4, U15.4, U16.4, U18.8, U20.6, U23.5
VCC_TIER1_5V0: C16.1, C42.1, R30.2, U6.3, U19.7

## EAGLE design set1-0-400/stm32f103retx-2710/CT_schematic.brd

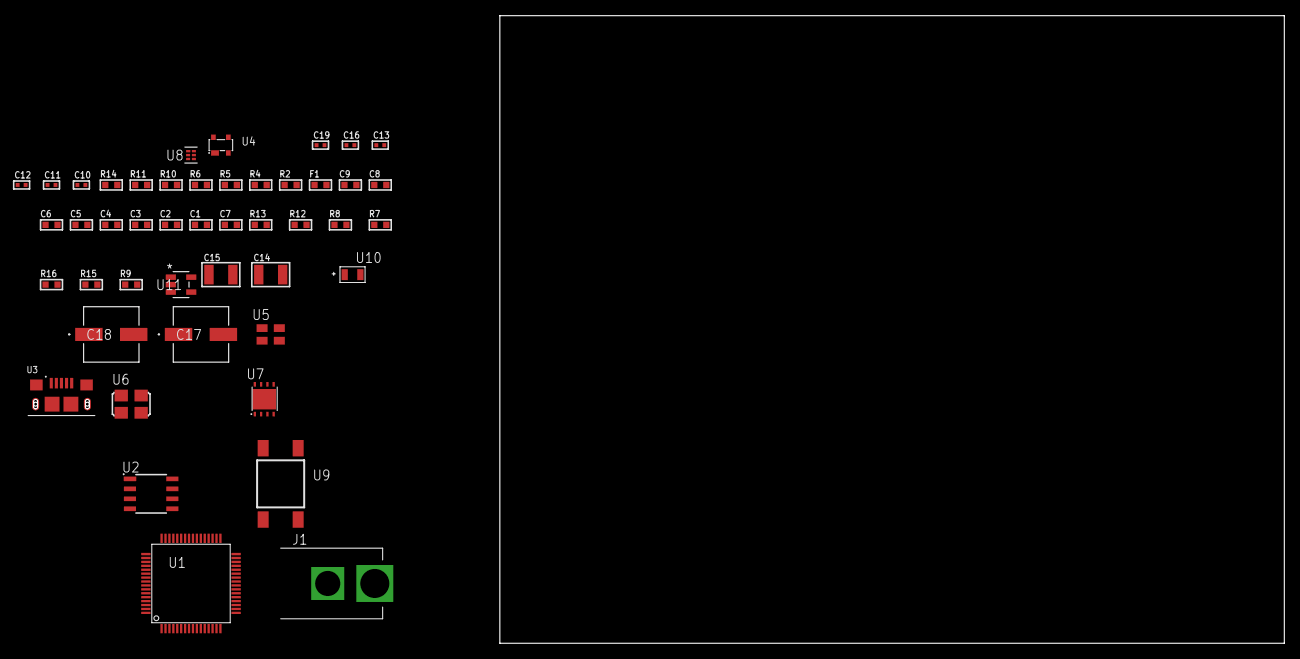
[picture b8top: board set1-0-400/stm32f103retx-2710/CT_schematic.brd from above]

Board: 2 copper layers, 159.4 x 80.0 mm, 46 parts (0 on the bottom side), 22 nets, no tracks yet.

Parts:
C1, C9: 1e-06; C0603
C2, C3, C4, C5, C6: 1e-07; C0603
C7: 4.7e-06; C0603
C8: 1e-08; C0603
C10, C11, C12, C13, C19: 1e-08; C0402
C14, C15: 1e-05; C1210
C16: 1e-07; C0402
C17, C18: 0.0001; EXV-9H
F1: 240.0; L0603
J1: PJ-037B; PJ-037B_PACKAGE
R2, R11: 1000.0; R0603
R4: 4700.0; R0603
R5, R6: 2200.0; R0603
R7, R8, R12, R13: 10000.0; R0603
R9: 100000.0; R0603
R10: 2231.0; R0603
R14: 9100.0; R0603
R15: 680000.0; R0603
R16: 120000.0; R0603
U1: stm32f103ret7; LQFP64
U2: M24M02-DRMN6TP; SOIC-8
U3: 10118193-0001LF; FCI_10118193-0001LF
U4: prtr5v0u2ax; SOT143B
U5: ASEK-32.768KHz-ECST; ASEK
U6: ASFL1-25MHZ-NCS; ASFL1
U7: LP3878SDX-ADJ/NOPB; WSON-8
U8: TPS3895ADRYR; SON-6
U9: 4-1437565-2; SW_4-1437565-2
U10: Q65110A2395; LGM67K-G1J2-24-Z
U11: nc7sz125m5x; NC7SZ125M5X

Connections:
CLK_U1_3: U1.3, U5.3
CLK_U1_5: U1.5, U6.3
GND: C1.2, C2.2, C3.2, C4.2, C5.2, C6.2, C7.2, C8.2, C9.2, C10.2, C11.2, C12.2, C13.2, C14.2, C15.2, C16.2, C17.2, C18.2, C19.2, J1.2, R2.2, R7.2, R8.2, R11.2, R14.2, R16.2, U1.12, U1.18, U1.31, U1.47, U1.63, U2.4, U3.5, U3.6, U3.7, U3.8, U3.9, U4.1, U5.2, U6.2, U7.3, U7.PAD, U8.2, U10.C, U11.1, U11.3
NET_U1_7: R4.1, U1.7, U11.4
NET_U1_13: C8.1, C9.1, F1.1, U1.13
NET_U1_58: R5.1, U1.58, U2.6
NET_U1_59: R6.1, U1.59, U2.5
NET_U1_60: R7.1, U1.60
NET_U1_62: U9.3, U9.4
NET_U2_3: R8.1, U2.3
NET_U4_4: U3.1, U4.4
NET_U7_1: C13.1, U7.1
NET_U7_6: R10.2, R11.1, U7.6
NET_U7_8: R9.1, U7.8
NET_U8_1: R13.1, R14.1, U8.1
NET_U8_3: R15.2, R16.1, U8.3
NET_U8_4: R12.1, U8.4, U11.2
NET_U9_1: R2.1, U9.1, U9.2
PROC_USB_DM: U1.44, U3.2, U4.3
PROC_USB_DP: U1.45, U3.3, U4.2
VCC_S1_15V3: C14.1, C17.1, C18.1, J1.1, R9.2, U7.4
VCC_TIER1_3V3: C1.1, C2.1, C3.1, C4.1, C5.1, C6.1, C7.1, C10.1, C11.1, C12.1, C15.1, C16.1, C19.1, F1.2, R4.2, R5.2, R6.2, R10.1, R12.2, R13.2, R15.1, U1.1, U1.19, U1.32, U1.48, U1.64, U2.8, U5.4, U6.4, U7.5, U8.6, U11.5
